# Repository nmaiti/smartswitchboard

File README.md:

# smartswitchboard

This repo contains all capsense design files

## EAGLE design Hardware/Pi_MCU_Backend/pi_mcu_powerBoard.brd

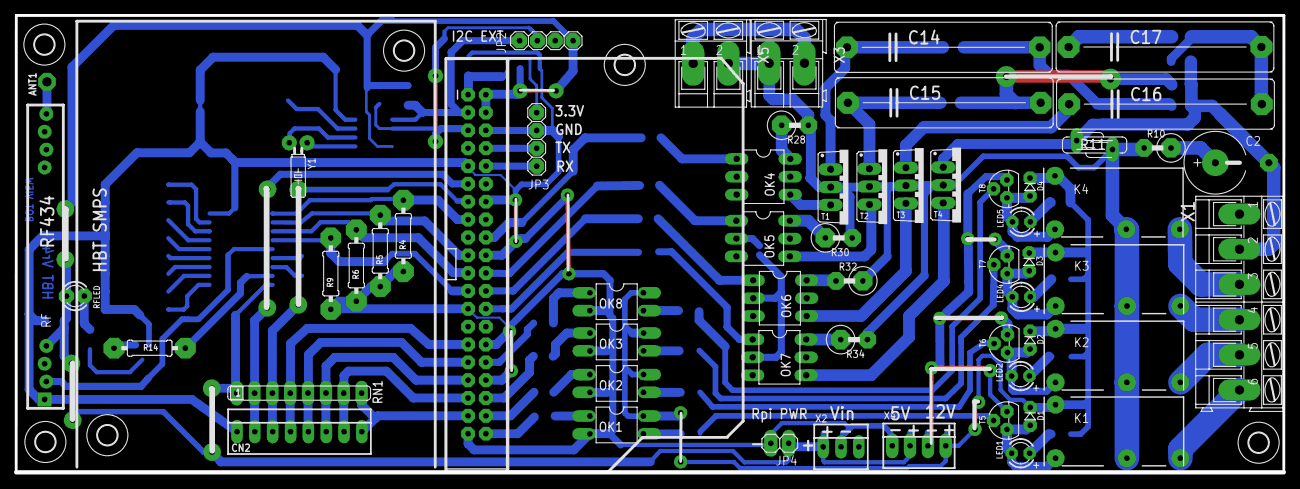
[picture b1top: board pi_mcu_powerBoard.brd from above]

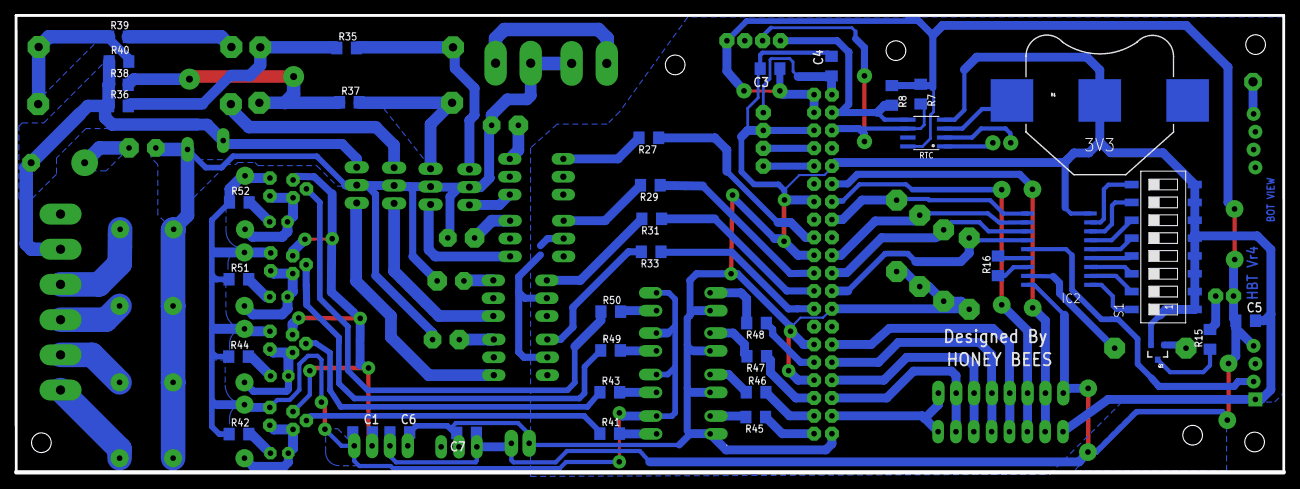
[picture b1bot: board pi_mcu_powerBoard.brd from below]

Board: 2 copper layers, 180.5 x 64.9 mm, 102 parts (37 on the bottom side), 93 nets.

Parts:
ANT1: PAD-01
B1: BATTCON_20MM
C1, C3, C4, C5, C6, C7: C1206
C2: E5R
C14, C16: 2.2uF/250VAC; C27.5B9
C15, C17: 3.3uF/250VAC; C27.5B9
CN2: Capsense I/P; 22-23-2081
D1, D2, D3, D4: D-2.5
IC2: HT680D; SOP18
JP1: RASPBERRYPI-B+-GPIO; 2X20-SHROUDED
JP2, JP3: 1X04
JP4: 1X02
K1, K2, K3, K4: RE030012; RE-SCHRACK
LED1, LED2, LED4, LED5: LED3MM
OK1, OK2, OK3, OK8: PC817; DIL04
OK4, OK5, OK6, OK7: MOC3041M; DIL06
Q2: MMBT2222A; SOT23-3
R4, R5, R6, R9: 0207/10
R7, R8: 4k7; 1206
R10: 0411V
R11: S07K11
R14: 10K; 0207/10
R15, R27, R29, R31, R33: 560R; 1206
R16: 33k; 1206
R28, R30, R32, R34: 470R/0.5W; 0411V
R35, R37, R39: 220K; 1206
R36, R38, R40: 2E2; 1206
R41, R42, R43, R44, R45, R46, R47, R48, R49, R50, R51, R52: 1k; 1206
RF: RF-LINK_RX
RFLED: LED3MM
RN1: SIL8
RTC: DS1307SO8; SO08
S1: SWS008; SMS-008
T1, T2, T3, T4: BTB16-V; TO220BV
T5, T6, T7, T8: BC547; TO92
U$3, U$4, U$5, U$6, U$7, U$8: 2,8
X1: AK300/6
X2: 22-23-2031
X3, X5: AK300/2
X4: 22-23-2041
Y1: 32.768KHz; TC26H

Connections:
(DIN)TE: IC2.14, RF.DATA@1
(VT)ADOUT: IC2.17, R14.2
+3V3: C4.1, JP1.1, JP1.17, JP3.1
+5V: C3.1, C5.1, C6.1, C7.1, IC2.18, JP1.2, JP1.4, JP2.1, JP4.1, R7.1, R8.1, RF.+5V@1, RFLED.A, RN1.1, RTC.8, X2.1, X4.2
+12V: C1.1, D1.C, D2.C, D3.C, D4.C, K1.A2, K2.A2, K3.A2, K4.A2, OK1.4, OK2.4, OK3.4, OK8.4, R42.1, R44.1, R51.1, R52.1, X4.4
-12V: C1.2, T5.1, T6.1, T7.1, T8.1, X4.3
A0: IC2.1, S1.16
A1: IC2.2, S1.15
A2: IC2.3, S1.14
A3: IC2.4, S1.13
A4: IC2.5, S1.12
A5: IC2.6, S1.11
A6: IC2.7, S1.10
A7: IC2.8, S1.9
DOWN: CN2.7, JP1.35, RN1.7
FAN_ON/OFF: CN2.8, JP1.37, RN1.8
FAN_REG: C2.-, R11.1, R36.1, R38.1, R40.1, T4.T1, X1.2
GND: B1.2, C3.2, C4.2, C5.2, C6.2, C7.2, CN2.1, IC2.9, JP1.6, JP1.9, JP1.14, JP1.20, JP1.25, JP1.30, JP1.34, JP1.39, JP2.2, JP3.2, JP4.2, OK1.2, OK2.2, OK3.2, OK4.2, OK5.2, OK6.2, OK7.2, OK8.2, Q2.2, R4.1, R5.1, R6.1, R9.1, RF.GND@1, RTC.4, S1.1, S1.2, S1.3, S1.4, S1.5, S1.6, S1.7, S1.8, X2.2, X4.1
L1: JP1.40, R45.1
L2: JP1.38, R46.2
L3: JP1.36, R47.1
L4: JP1.32, R48.1
LEVEL1: JP1.18, R27.1
LEVEL2: JP1.22, R29.1
LEVEL3: JP1.24, R31.1
LEVEL4: JP1.26, R33.1
LINE: K1.14, K2.14, K3.14, K4.14, R10.2, R11.2, R28.2, R30.2, R32.1, R34.2, T1.T2, T2.T2, T3.T2, T4.T2, X3.1, X5.2
unnamed: OK6.1, R31.2
unnamed: OK4.1, R27.2
unnamed: OK5.1, R29.2
unnamed: OK4.6, R28.1
unnamed: OK7.1, R33.2
unnamed: OK1.3, R41.2
unnamed: R41.1, T5.2
unnamed: D1.A, K1.A1, LED1.K, T5.3
unnamed: LED1.A, R42.2
unnamed: OK1.1, R45.2
unnamed: RTC.2, Y1.2
unnamed: OK2.1, R46.1
unnamed: OK2.3, R43.2
unnamed: R43.1, T6.2
unnamed: C2.+, R10.1
unnamed: D2.A, K2.A1, LED2.K, T6.3
unnamed: Q2.1, R14.1
unnamed: RTC.1, Y1.1
unnamed: K3.11, X1.4
unnamed: B1.1, RTC.3
unnamed: Q2.3, R15.1
unnamed: LED2.A, R44.2
unnamed: K1.11, X1.6
unnamed: R15.2, RFLED.K
unnamed: K2.11, X1.5
unnamed: OK5.6, R30.1
unnamed: OK6.6, R32.2
unnamed: ANT1.1, RF.ANT
unnamed: OK3.1, R47.2
unnamed: OK8.3, R50.2
unnamed: OK7.6, R34.1
unnamed: OK3.3, R49.2
unnamed: R49.1, T7.2
unnamed: R50.1, T8.2
unnamed: D3.A, K3.A1, LED4.K, T7.3
unnamed: K4.11, X1.3
unnamed: LED4.A, R51.2
unnamed: D4.A, K4.A1, LED5.K, T8.3
unnamed: LED5.A, R52.2
unnamed: OK8.1, R48.2
unnamed: OK4.4, T1.G
unnamed: C14.1, R35.2, T1.T1
unnamed: C14.2, R35.1, R36.2
unnamed: OK5.4, T2.G
unnamed: C15.1, R37.2, T2.T1
unnamed: C15.2, R37.1, R38.2
unnamed: OK6.4, T3.G
unnamed: C16.1, C17.1, R39.2, T3.T1
unnamed: C16.2, C17.2, R39.1, R40.2
unnamed: OK7.4, T4.G
NEUTRAL: X1.1, X3.2, X5.1
OSC1: IC2.16, R16.1
OSC2: IC2.15, R16.2
RFD0: IC2.10, JP1.15, R4.2
RFD1: IC2.11, JP1.19, R5.2
RFD2: IC2.12, JP1.21, R6.2
RFD3: IC2.13, JP1.23, R9.2
RX: JP1.10, JP3.4
SCL: JP1.5, JP2.3, R7.2, RTC.6
SDA: JP1.3, JP2.4, R8.2, RTC.5
SW-1: CN2.2, JP1.11, RN1.2
SW-2: CN2.3, JP1.13, RN1.3
SW-3: CN2.4, JP1.29, RN1.4
SW-4: CN2.5, JP1.31, RN1.5
TX: JP1.8, JP3.3
UP: CN2.6, JP1.33, RN1.6

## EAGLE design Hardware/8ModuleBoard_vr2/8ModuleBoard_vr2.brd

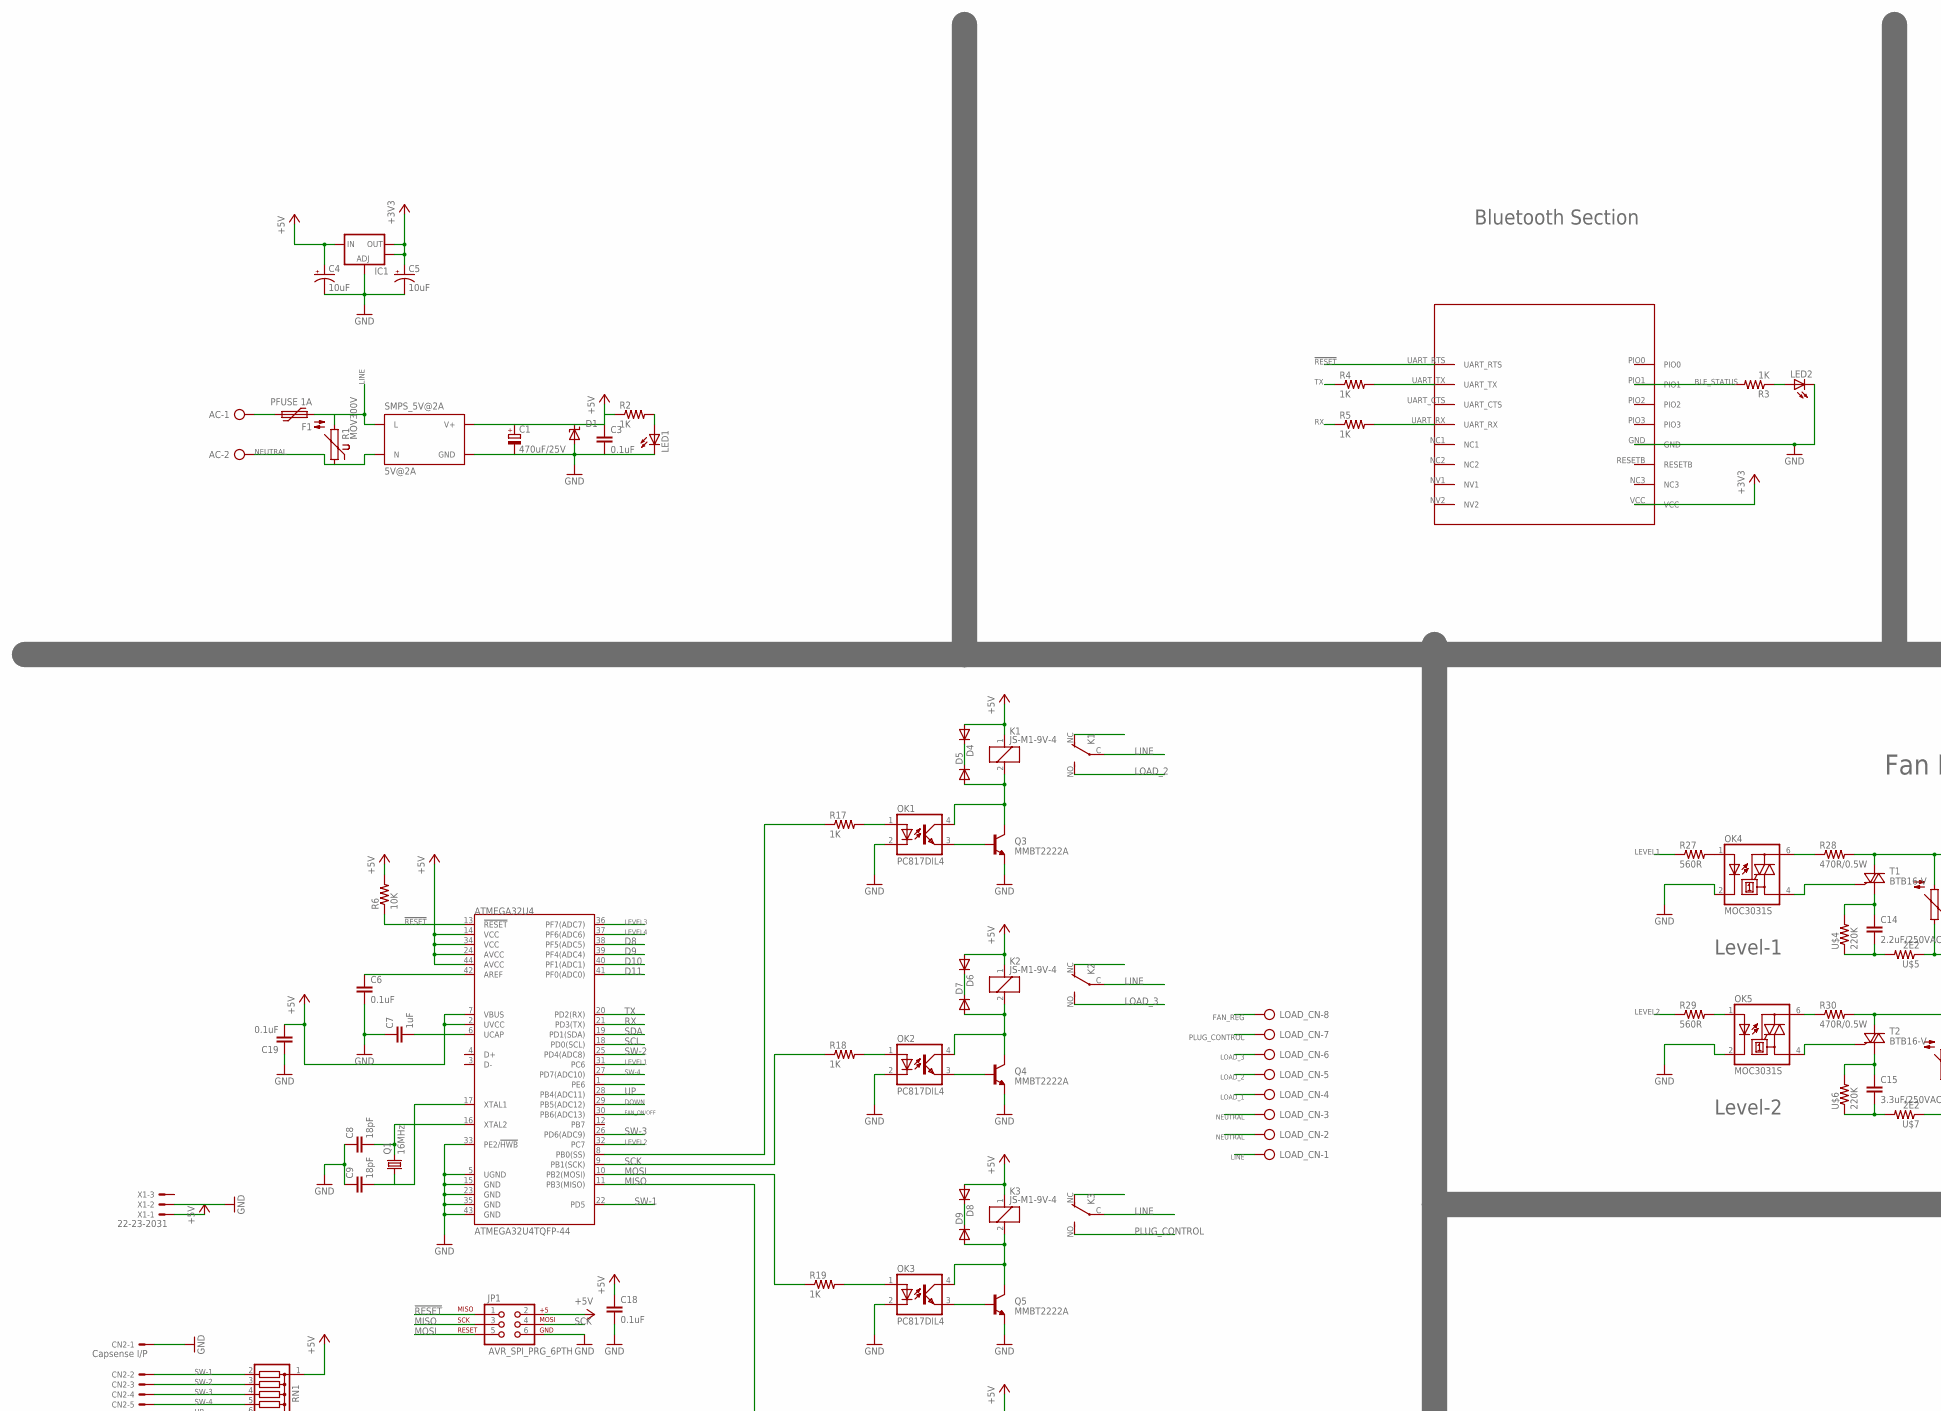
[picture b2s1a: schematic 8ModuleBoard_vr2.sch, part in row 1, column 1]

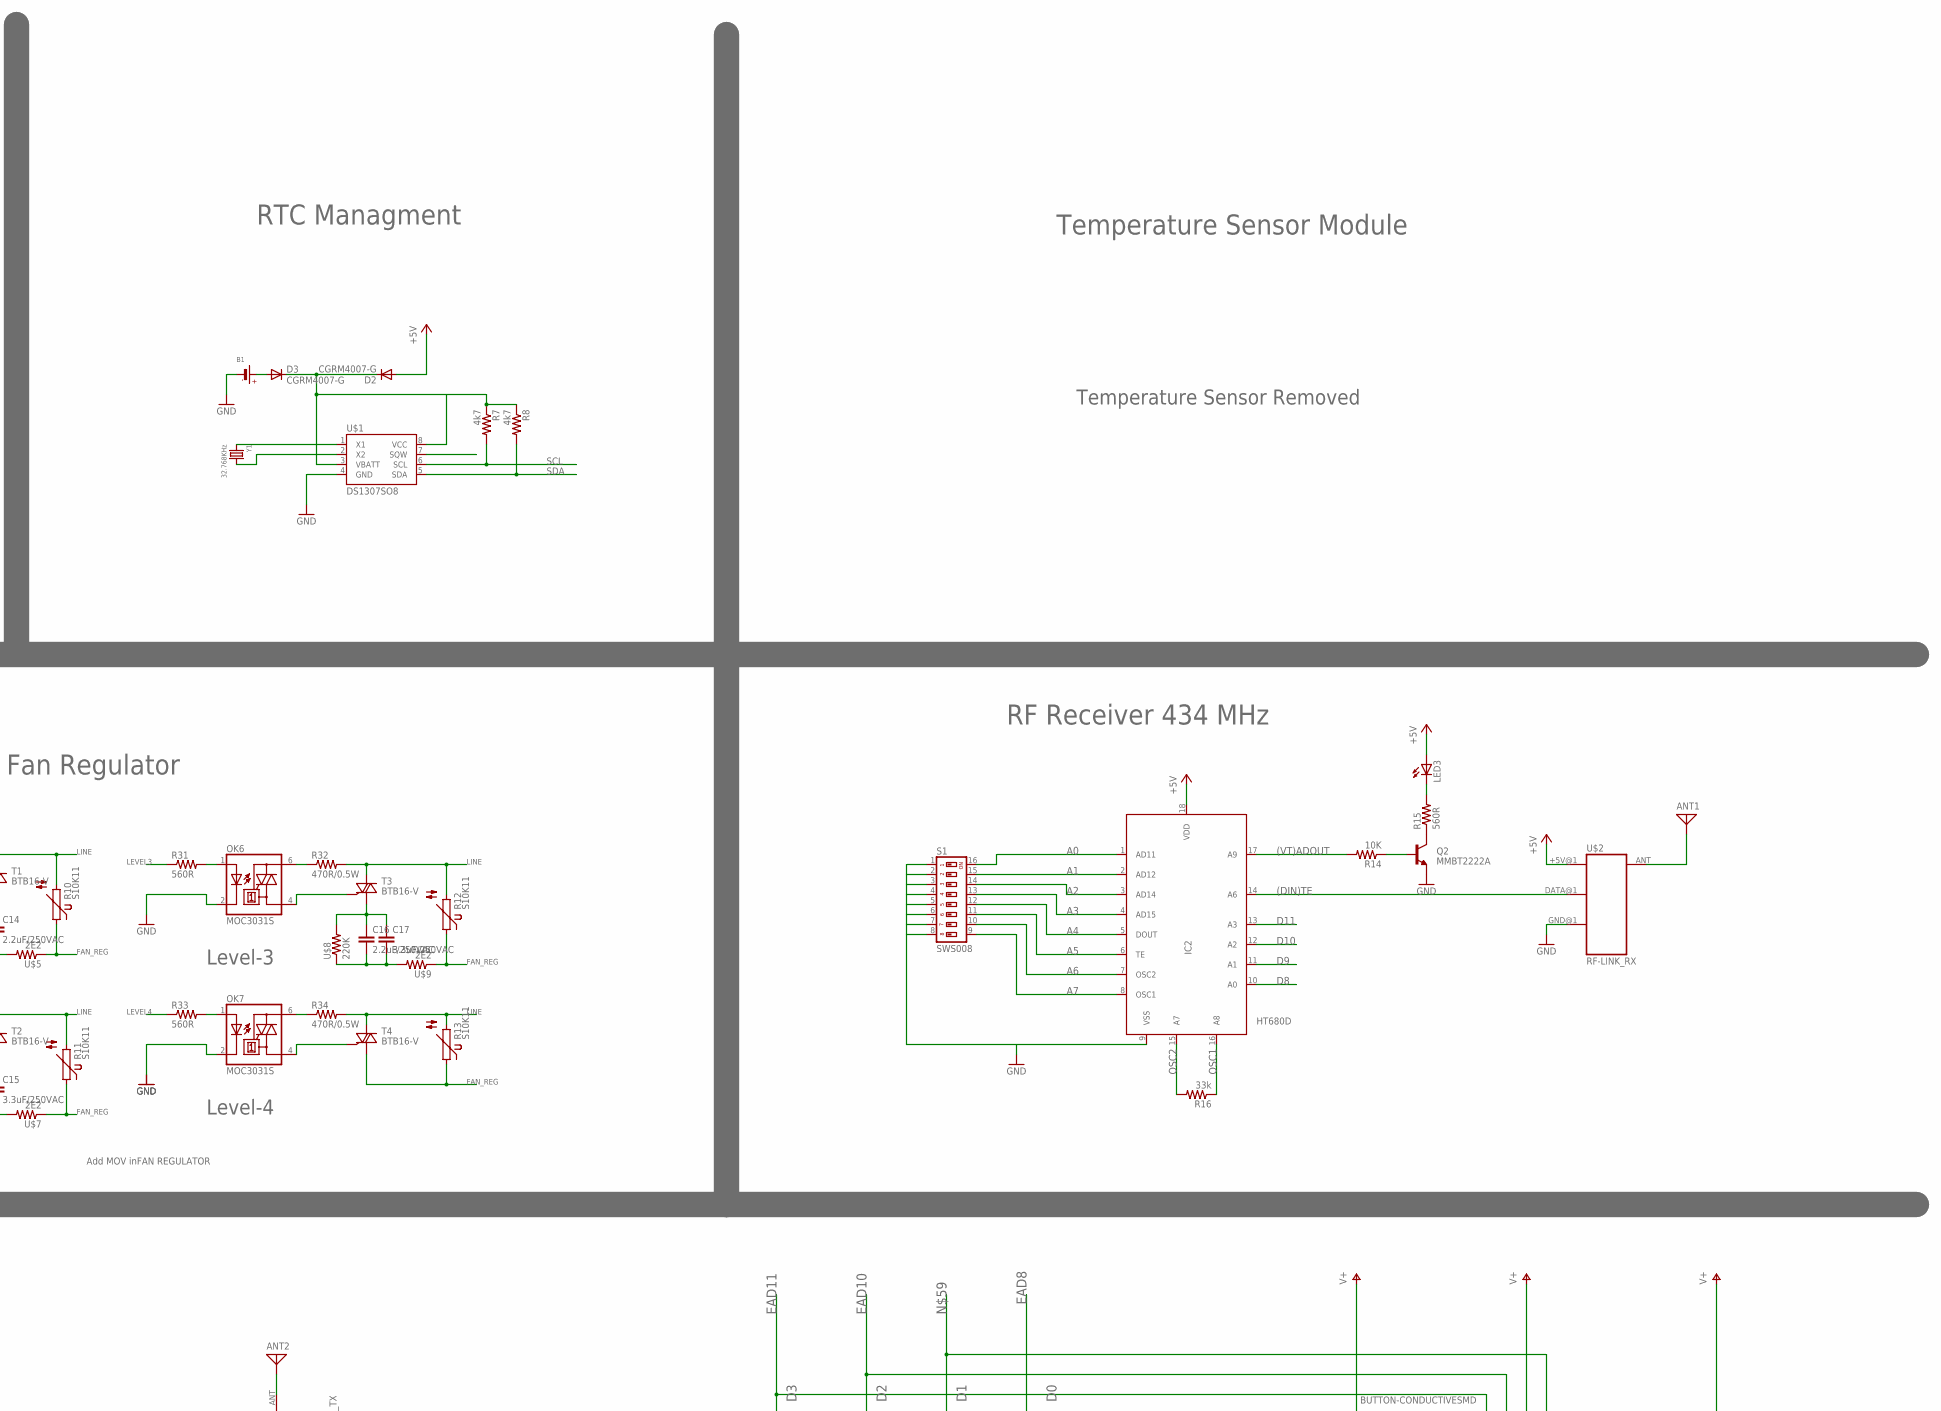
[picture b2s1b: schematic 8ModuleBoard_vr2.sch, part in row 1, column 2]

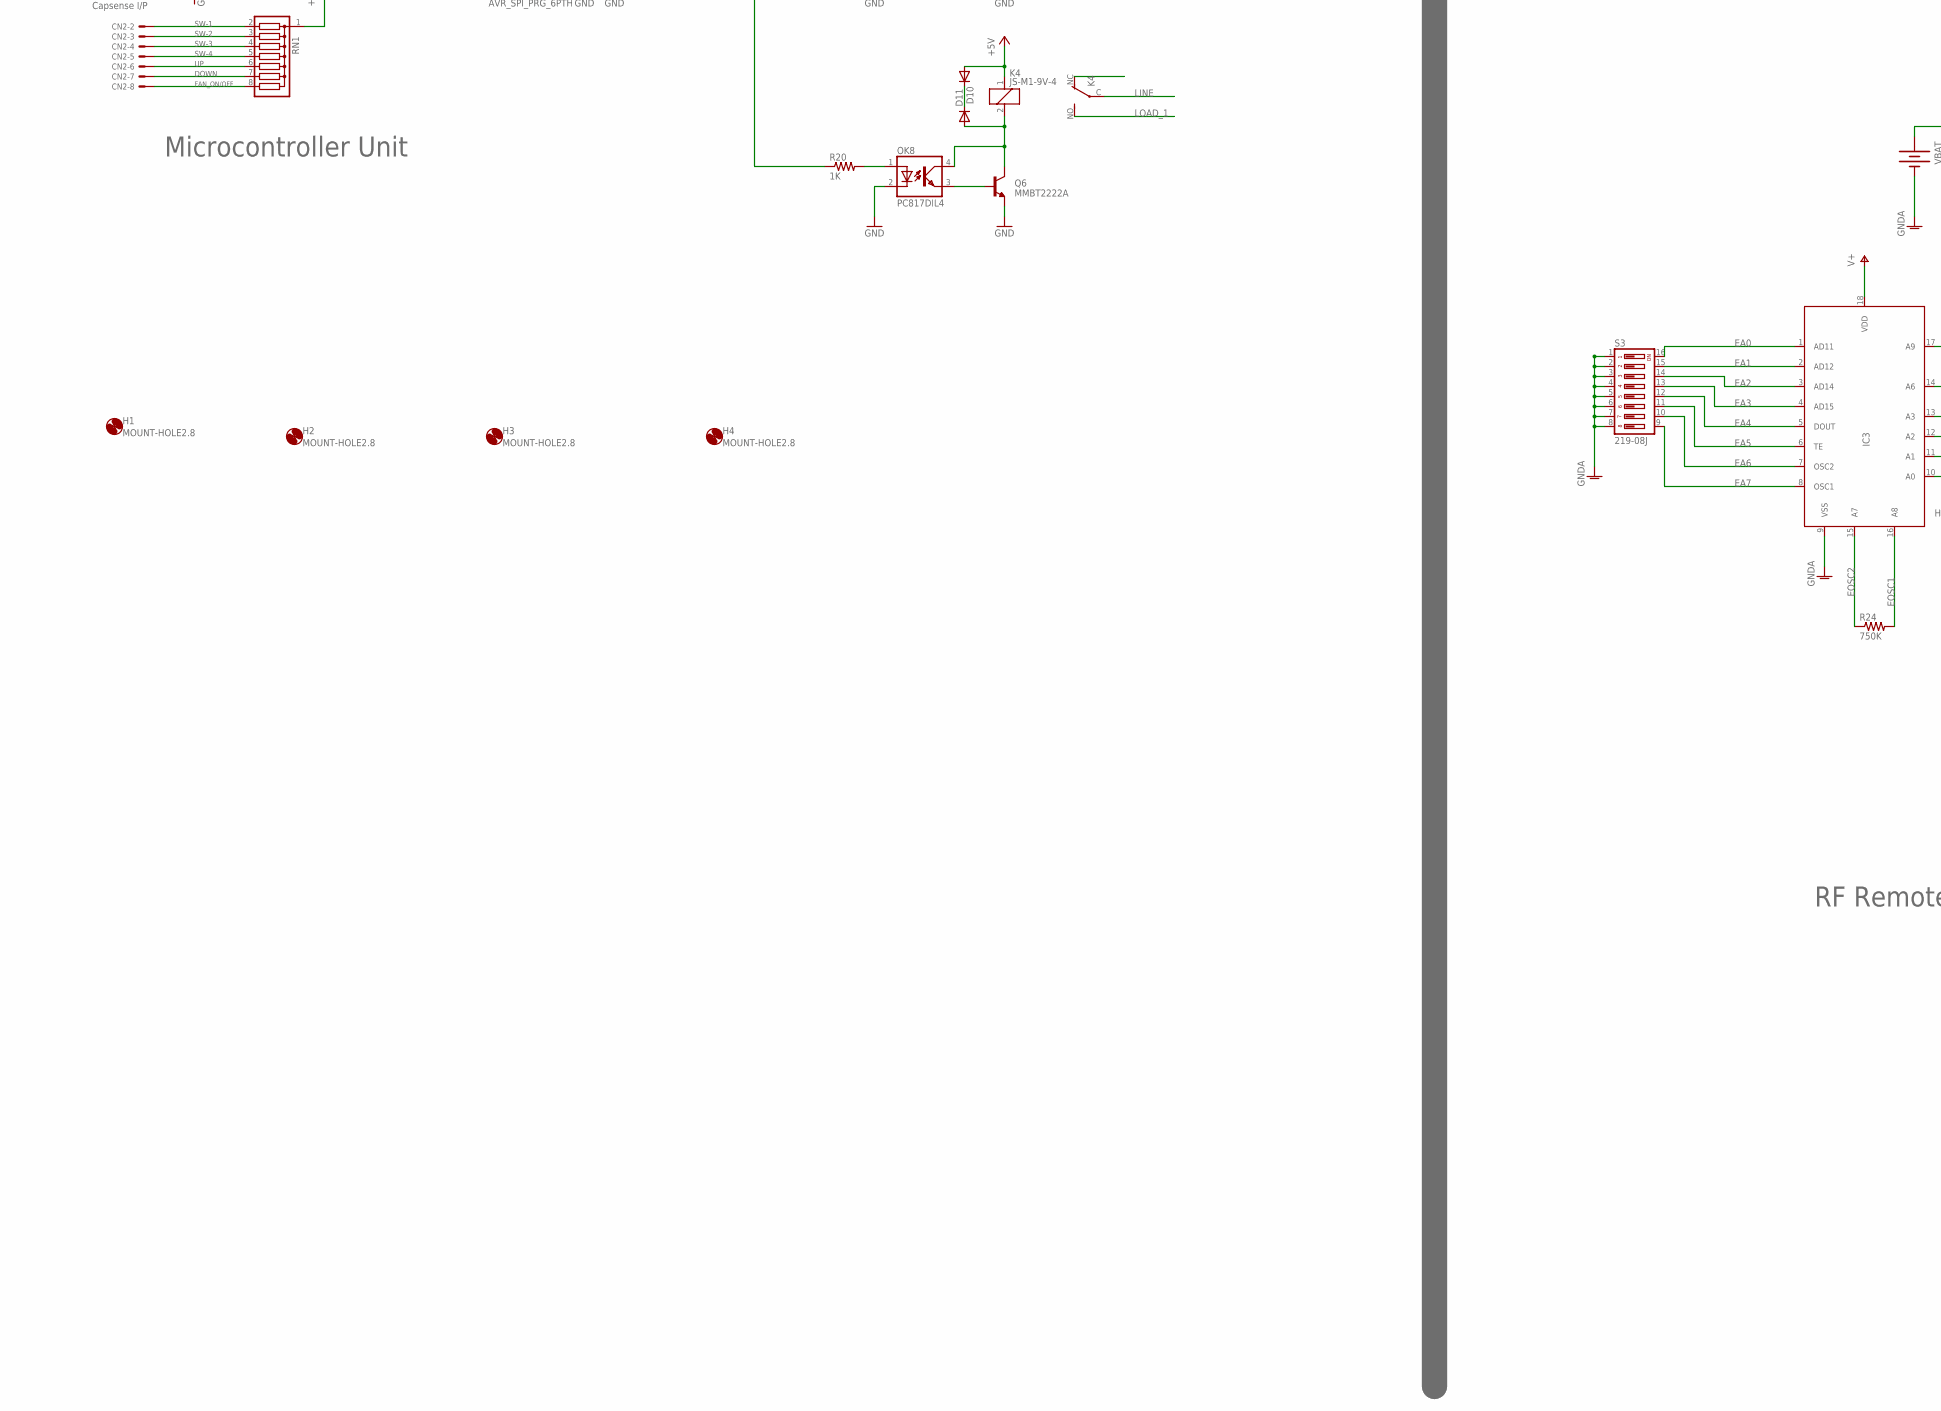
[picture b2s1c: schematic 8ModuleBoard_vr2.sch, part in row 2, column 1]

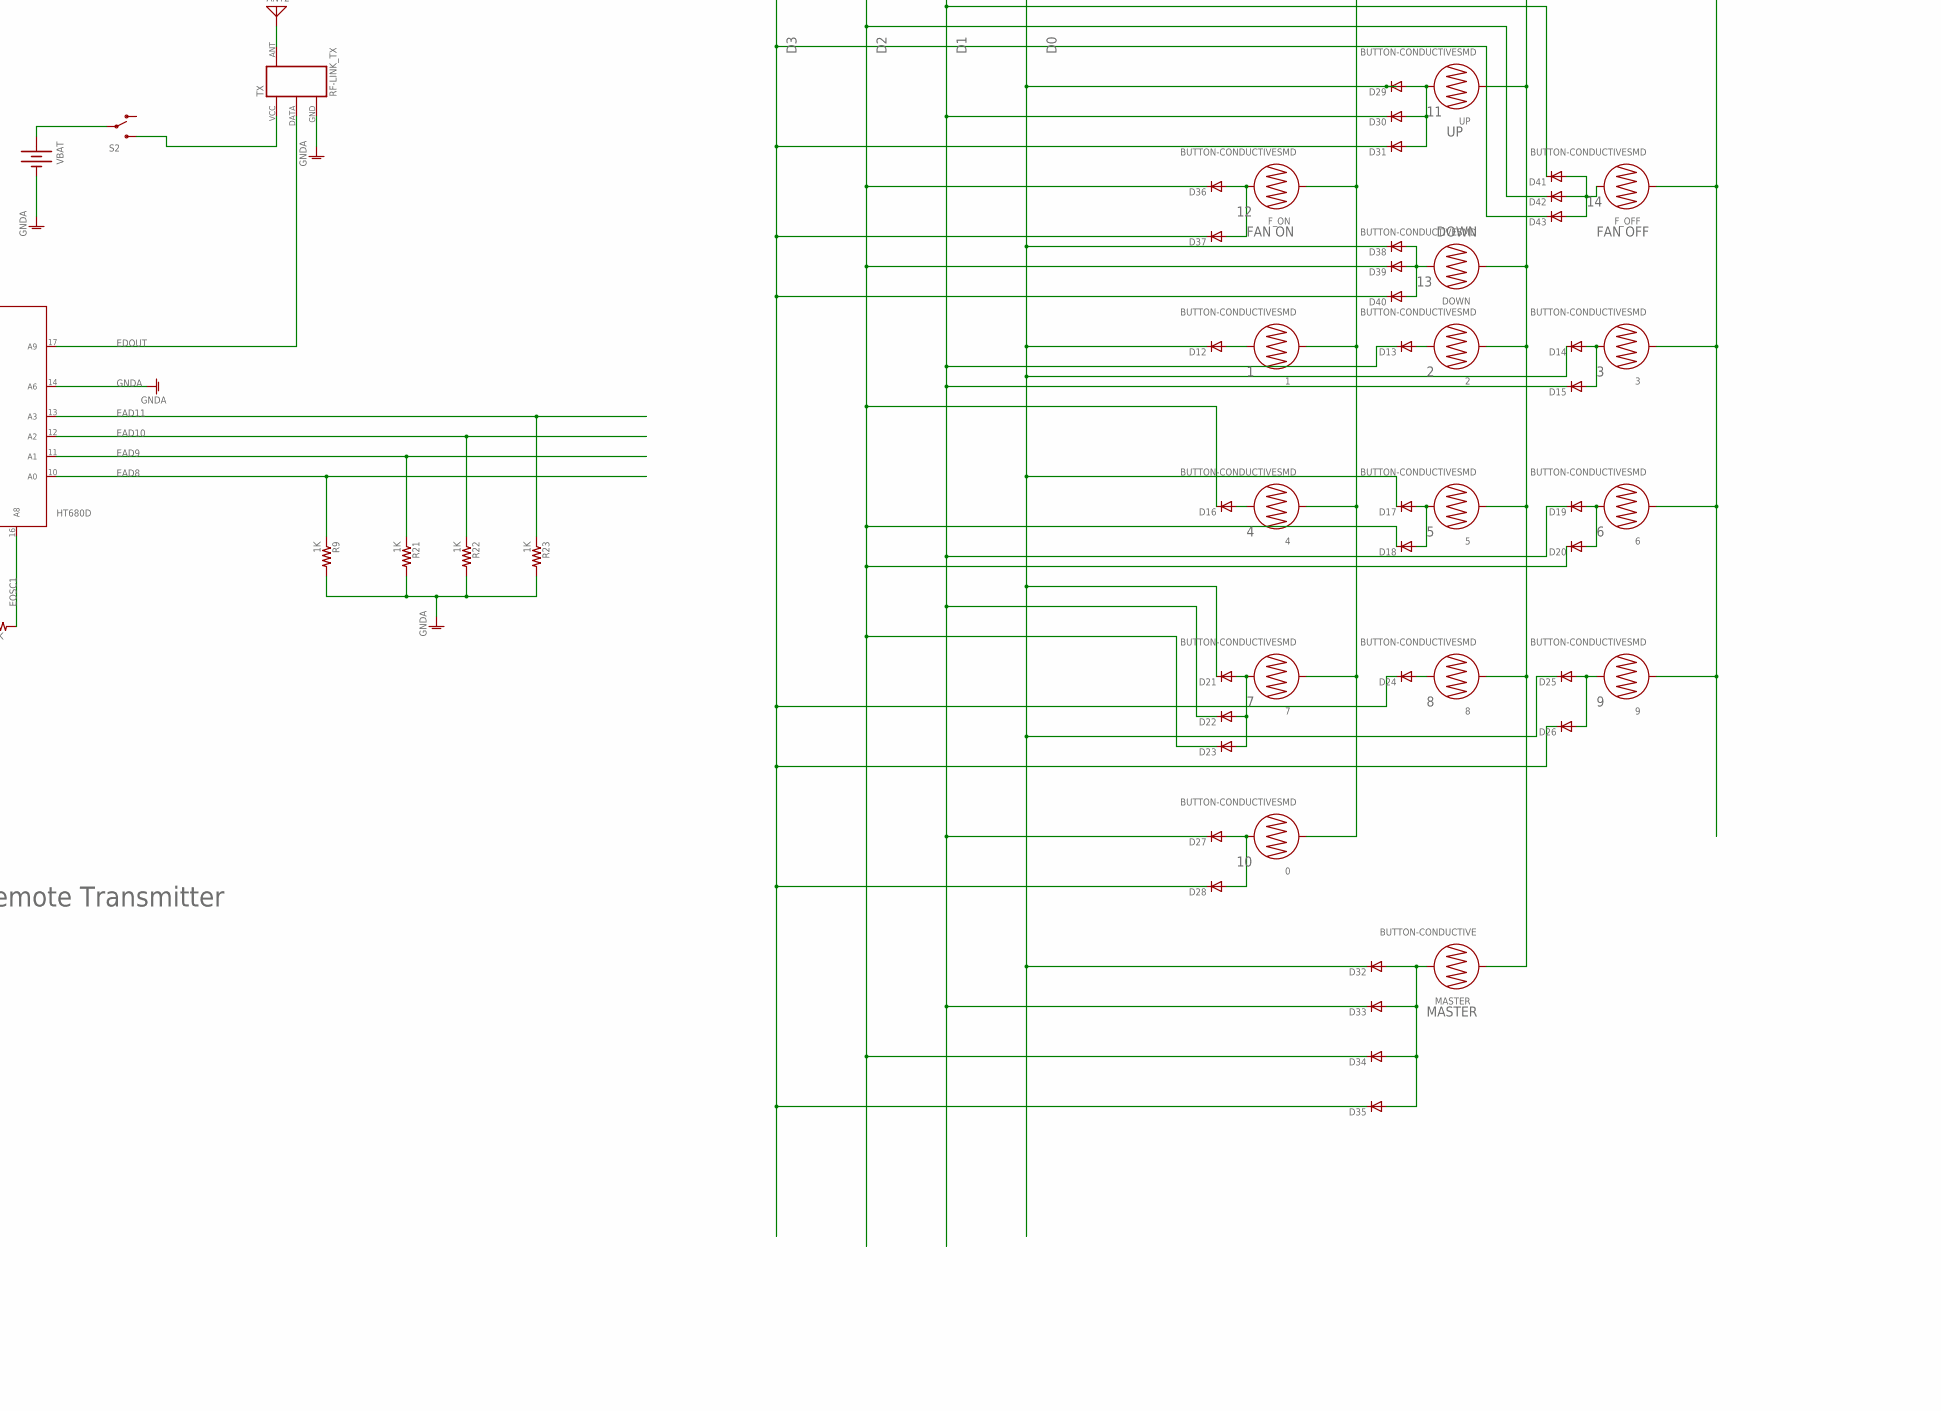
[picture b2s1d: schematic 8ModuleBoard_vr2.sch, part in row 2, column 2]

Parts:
0, 1, 2, 3, 4, 5, 6, 7, 8, 9: BUTTON-CONDUCTIVESMD; BUTTON-CONDUCTIVE
AC: AK300/2
ANT1, ANT2: ANTENNA; PAD-01
ATMEGA32U4: ATMEGA32U4TQFP-44; TQFP44
B1: BATTERYCR2032; CR2032
C1: 470uF/25V; E5-8,5
C3, C6, C18, C19: 0.1uF; 1206
C4, C5: 10uF; EIA3216
C7: 1uF; 1206
C8, C9: 18pF; 1206
C14, C16: 2.2uF/250VAC; C27.5B9
C15, C17: 3.3uF/250VAC; C27.5B9
CN2: Capsense I/P; 22-23-2081
D1: SUPPRESSOR-SMBJ; SMBJ
D2, D3: CGRM4007-G; SOD-123_MINI-SMA
D4, D5, D6, D7, D8, D9, D10, D11, D12, D13, D14, D15, D16, D17, D18, D19, D20, D21, D22, D23, D24, D25, D26, D27, D28, D29, D30, D31, D32, D33, D34, D35, D36, D37, D38, D39, D40, D41, D42, D43: DIODE-SOD123; SOD123
DOWN: BUTTON-CONDUCTIVESMD; BUTTON-CONDUCTIVE
F1: PFUSE 1A; MF-5,1B
F_OFF: BUTTON-CONDUCTIVESMD; BUTTON-CONDUCTIVE
F_ON: BUTTON-CONDUCTIVESMD; BUTTON-CONDUCTIVE
H1, H2, H3, H4: MOUNT-HOLE2.8; 2,8
IC1: V_REG_LM1117SOT223; SOT223
IC2, IC3: HT680D; SOP18
JP1: AVR_SPI_PRG_6PTH; 2X3
K1, K2, K3, K4: JS-M1-9V-4; JS-M
LED1, LED2, LED3: LEDSML1206; SML1206
LOAD_CN: AK300/8
MASTER: BUTTON-CONDUCTIVE; BUTTON-CONDUCTIVE-MINI
OK1, OK2, OK3, OK8: PC817DIL4; DIL4-SMD
OK4: MOC3031S; DIL6-SMD
OK5, OK6, OK7: MOC3031S; DIL6-SMD; MPN MOC3031SM
Q1: 16MHz; HC49UP
Q2, Q3, Q4, Q5, Q6: MMBT2222A; SOT23-3
R1: MOV300V; S10K11
R2, R3, R4, R5, R9, R17, R18, R19, R20, R21, R22, R23: 1K; 1206
R6, R14: 10K; 1206
R7, R8: 4k7; 1206
R10, R11, R12, R13: S10K11
R15, R27, R29, R31, R33: 560R; 1206
R16: 33k; 1206
R24: 750K; 1206
R28, R30, R32, R34: 470R/0.5W; 0411V
RN1: G07R; SIL8
S1: SWS008; SMS-008
S2: SWITCH-SPDT-SMD-A; SWITCH-SPST-SMD-A
S3: 219-08J; CTS-219-08J
SMPS_5V@2A: 5V@2A; MKS1854-6-0-404
T1, T2, T3, T4: BTB16-V; TO220BV
TX: RF-LINK_TX
U$1: DS1307SO8; SO08
U$2: RF-LINK_RX
U$3: HM-11
U$4, U$6, U$8: 220K; 1206
U$5, U$7, U$9: 2E2; 1206
UP: BUTTON-CONDUCTIVESMD; BUTTON-CONDUCTIVE
VBAT: BATTERY20SMD; BATTCON_20MM
X1: 22-23-2031
Y1: 32.768KHz; CRYSTAL_CYL_2X6MM_SMT

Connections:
!RESET: ATMEGA32U4.13 (!RESET), JP1.1, R6.1, U$3.UART_RTS
(DIN)TE: IC2.14 (A6), U$2.DATA@1 (DATA)
(VT)ADOUT: IC2.17 (A9), R14.2
+3V3: C5.A (+), IC1.2 (OUT), IC1.4 (OUT), U$3.VCC
+5V: ATMEGA32U4.2 (UVCC), ATMEGA32U4.7 (VBUS), ATMEGA32U4.14 (VCC), ATMEGA32U4.24 (AVCC), ATMEGA32U4.34 (VCC), ATMEGA32U4.44 (AVCC), C1.+, C3.1, C4.A (+), C18.1, C19.2, D1.C, D2.A, D4.A, D6.A, D8.A, D10.A, IC1.3 (IN), IC2.18 (VDD), JP1.2, K1.1, K2.1, K3.1, K4.1, LED3.A, R2.1, R6.2, RN1.1, SMPS_5V@2A.3 (V+), U$2.+5V@1 (+5V), X1.1
A0: IC2.1 (AD11), S1.16
A1: IC2.2 (AD12), S1.15
A2: IC2.3 (AD14), S1.14
A3: IC2.4 (AD15), S1.13
A4: IC2.5 (DOUT), S1.12
A5: IC2.6 (TE), S1.11
A6: IC2.7 (OSC2), S1.10
A7: IC2.8 (OSC1), S1.9
BLE_STATUS: R3.2, U$3.PIO1
D8: ATMEGA32U4.38 (PF5(ADC5)), IC2.10 (A0)
D9: ATMEGA32U4.39 (PF4(ADC4)), IC2.11 (A1)
D10: ATMEGA32U4.40 (PF1(ADC1)), IC2.12 (A2)
D11: ATMEGA32U4.41 (PF0(ADC0)), IC2.13 (A3)
DOWN: ATMEGA32U4.29 (PB5(ADC12)), CN2.7, RN1.7
EA0: IC3.1 (AD11), S3.16
EA1: IC3.2 (AD12), S3.15
EA2: IC3.3 (AD14), S3.14
EA3: IC3.4 (AD15), S3.13
EA4: IC3.5 (DOUT), S3.12
EA5: IC3.6 (TE), S3.11
EA6: IC3.7 (OSC2), S3.10
EA7: IC3.8 (OSC1), S3.9
EAD8: D12.C, D14.C, D17.C, D21.C, D25.C, D29.C, D32.C, D38.C, IC3.10 (A0), R9.1
EAD9: IC3.11 (A1), R21.1
EAD10: D16.C, D18.C, D20.C, D23.C, D34.C, D36.C, D39.C, D42.C, IC3.12 (A2), R22.1
EAD11: D24.C, D26.C, D28.C, D31.C, D35.C, D37.C, D40.C, D43.C, IC3.13 (A3), R23.1
EDOUT: IC3.17 (A9), TX.DATA
EOSC1: IC3.16 (A8), R24.2
EOSC2: IC3.15 (A7), R24.1
FAN_ON/OFF: ATMEGA32U4.30 (PB6(ADC13)), CN2.8, RN1.8
FAN_REG: LOAD_CN.8, R10.1, R11.1, R12.1, R13.1, T4.T1 (A1), U$5.1, U$7.1, U$9.1
GND: ATMEGA32U4.5 (UGND), ATMEGA32U4.15 (GND), ATMEGA32U4.23 (GND), ATMEGA32U4.33 (PE2/!HWB), ATMEGA32U4.35 (GND), ATMEGA32U4.43 (GND), B1.-, C1.-, C3.2, C4.C (-), C5.C (-), C6.2, C7.1, C8.1, C9.1, C18.2, C19.1, CN2.1, D1.A, IC1.1 (ADJ), IC2.9 (VSS), JP1.6, LED1.C, LED2.C, OK1.2 (C), OK2.2 (C), OK3.2 (C), OK4.2 (C), OK5.2 (C), OK6.2 (C), OK7.2 (C), OK8.2 (C), Q2.2 (E), Q3.2 (E), Q4.2 (E), Q5.2 (E), Q6.2 (E), S1.1, S1.2, S1.3, S1.4, S1.5, S1.6, S1.7, S1.8, SMPS_5V@2A.4 (GND), U$1.4 (GND), U$2.GND@1 (GND), U$3.GND, X1.2
GNDA: IC3.9 (VSS), IC3.14 (A6), R9.2, R21.2, R22.2, R23.2, S3.1, S3.2, S3.3, S3.4, S3.5, S3.6, S3.7, S3.8, TX.GND, VBAT.2 (-)
LEVEL1: ATMEGA32U4.31 (PC6), R27.1
LEVEL2: ATMEGA32U4.32 (PC7), R29.1
LEVEL3: ATMEGA32U4.36 (PF7(ADC7)), R31.1
LEVEL4: ATMEGA32U4.37 (PF6(ADC6)), R33.1
LINE: F1.1, K1.C, K2.C, K3.C, K4.C, LOAD_CN.1, R1.2, R10.2, R11.2, R12.2, R13.2, R28.2, R30.2, R32.2, R34.2, SMPS_5V@2A.1 (L), T1.T2 (A2), T2.T2 (A2), T3.T2 (A2), T4.T2 (A2)
LOAD_1: K4.NO (S), LOAD_CN.4
LOAD_2: K1.NO (S), LOAD_CN.5
LOAD_3: K2.NO (S), LOAD_CN.6
MISO: ATMEGA32U4.11 (PB3(MISO)), JP1.3, R20.1
MOSI: ATMEGA32U4.10 (PB2(MOSI)), JP1.5, R19.1
unnamed: OK6.1 (A), R31.2
unnamed: OK4.1 (A), R27.2
unnamed: OK5.1 (A), R29.2
unnamed: OK4.6 (A2), R28.1
unnamed: OK7.1 (A), R33.2
unnamed: R4.2, U$3.UART_TX
unnamed: ATMEGA32U4.6 (UCAP), C7.2
unnamed: Q2.1 (B), R14.1
unnamed: LED2.A, R3.1
unnamed: ATMEGA32U4.42 (AREF), C6.1
unnamed: R5.2, U$3.UART_RX
unnamed: U$1.1 (X1), Y1.1
unnamed: U$1.2 (X2), Y1.2
unnamed: D2.C, D3.C, R7.1, R8.1, U$1.3 (VBATT), U$1.8 (VCC)
unnamed: LED1.A, R2.2
unnamed: B1.+, D3.A
unnamed: 1.2, D12.A
unnamed: 2.2, D13.A
unnamed: ATMEGA32U4.16 (XTAL2), C8.2, Q1.2
unnamed: ATMEGA32U4.17 (XTAL1), C9.2, Q1.1
unnamed: Q2.3 (C), R15.1
unnamed: S2.2, VBAT.1 (+)
unnamed: LED3.C, R15.2
unnamed: S2.3 (S), TX.VCC (+5V)
unnamed: OK5.6 (A2), R30.1
unnamed: OK6.6 (A2), R32.1
unnamed: ANT1.1, U$2.ANT
unnamed: OK1.3 (EMIT), Q3.1 (B)
unnamed: D5.A, K1.2, OK1.4 (COL), Q3.3 (C)
unnamed: OK7.6 (A2), R34.1
unnamed: 3.2, D14.A, D15.A
unnamed: AC.1, F1.2
unnamed: D4.C, D5.C
unnamed: ANT2.1, TX.ANT
unnamed: OK1.1 (A), R17.2
unnamed: 4.2, D16.A
unnamed: OK2.3 (EMIT), Q4.1 (B)
unnamed: 5.2, D17.A, D18.A
unnamed: D7.A, K2.2, OK2.4 (COL), Q4.3 (C)
unnamed: D6.C, D7.C
unnamed: 6.2, D19.A, D20.A
unnamed: 7.2, D21.A, D22.A, D23.A
unnamed: OK2.1 (A), R18.2
unnamed: OK3.3 (EMIT), Q5.1 (B)
unnamed: 0.2, D27.A, D28.A
unnamed: D9.A, K3.2, OK3.4 (COL), Q5.3 (C)
unnamed: OK4.4 (A1), T1.G
unnamed: C14.1, T1.T1 (A1), U$4.2
unnamed: C14.2, U$4.1, U$5.2
unnamed: D8.C, D9.C
unnamed: D13.C, D15.C, D19.C, D22.C, D27.C, D30.C, D33.C, D41.C
unnamed: D29.A, D30.A, D31.A, UP.2
unnamed: 8.2, D24.A
unnamed: OK5.4 (A1), T2.G
unnamed: C15.1, T2.T1 (A1), U$6.2
unnamed: C15.2, U$6.1, U$7.2
unnamed: OK3.1 (A), R19.2
unnamed: OK8.3 (EMIT), Q6.1 (B)
unnamed: D11.A, K4.2, OK8.4 (COL), Q6.3 (C)
unnamed: D36.A, D37.A, F_ON.2
unnamed: D10.C, D11.C
unnamed: OK6.4 (A1), T3.G
unnamed: C16.1, C17.1, T3.T1 (A1), U$8.2
unnamed: C16.2, C17.2, U$8.1, U$9.2
unnamed: 9.2, D25.A, D26.A
unnamed: D38.A, D39.A, D40.A, DOWN.2
unnamed: D32.A, D33.A, D34.A, D35.A, MASTER.2
unnamed: OK8.1 (A), R20.2
unnamed: OK7.4 (A1), T4.G
unnamed: D41.A, D42.A, D43.A, F_OFF.2
unnamed: ATMEGA32U4.8 (PB0(SS)), R17.1
NEUTRAL: AC.2, LOAD_CN.2, LOAD_CN.3, R1.1, SMPS_5V@2A.2 (N)
OSC1: IC2.16 (A8), R16.1
OSC2: IC2.15 (A7), R16.2
PLUG_CONTROL: K3.NO (S), LOAD_CN.7
RX: ATMEGA32U4.21 (PD3(TX)), R5.1
SCK: ATMEGA32U4.9 (PB1(SCK)), JP1.4, R18.1
SCL: ATMEGA32U4.18 (PD0(SCL)), R7.2, U$1.6 (SCL)
SDA: ATMEGA32U4.19 (PD1(SDA)), R8.2, U$1.5 (SDA)
SW-1: ATMEGA32U4.22 (PD5), CN2.2, RN1.2
SW-2: ATMEGA32U4.25 (PD4(ADC8)), CN2.3, RN1.3
SW-3: ATMEGA32U4.26 (PD6(ADC9)), CN2.4, RN1.4
SW-4: ATMEGA32U4.27 (PD7(ADC10)), CN2.5, RN1.5
TX: ATMEGA32U4.20 (PD2(RX)), R4.1
UP: ATMEGA32U4.28 (PB4(ADC11)), CN2.6, RN1.6
V+: 0.1, 1.1, 2.1, 3.1, 4.1, 5.1, 6.1, 7.1, 8.1, 9.1, DOWN.1, F_OFF.1, F_ON.1, IC3.18 (VDD), MASTER.1, UP.1

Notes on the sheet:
Microcontroller Unit
Level-1
Level-2
Level-3
Level-4
Fan Regulator
Bluetooth Section
Add MOV inFAN REGULATOR
RTC Managment
Temperature Sensor Module
RF Receiver 434 MHz
Temperature Sensor Removed
MASTER
FAN ON
FAN OFF
DOWN
RF Remote Transmitter

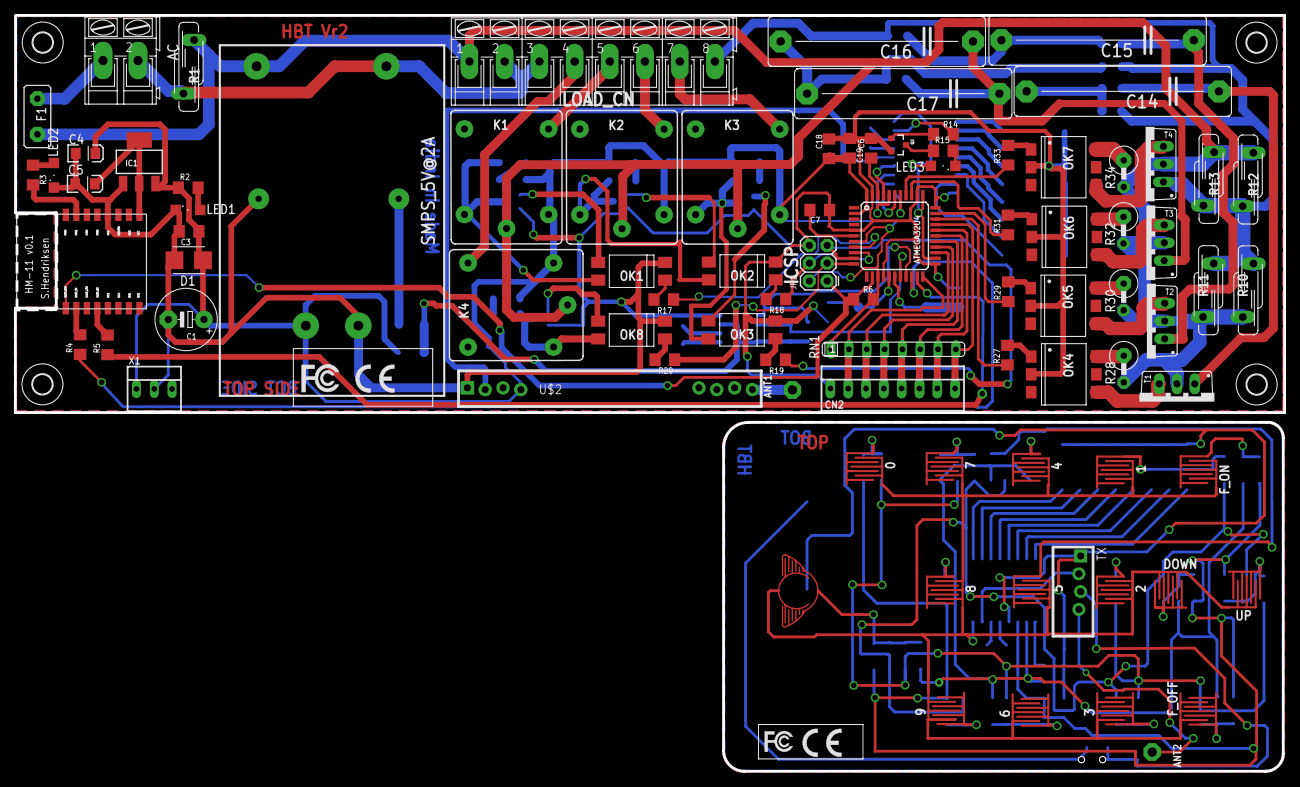
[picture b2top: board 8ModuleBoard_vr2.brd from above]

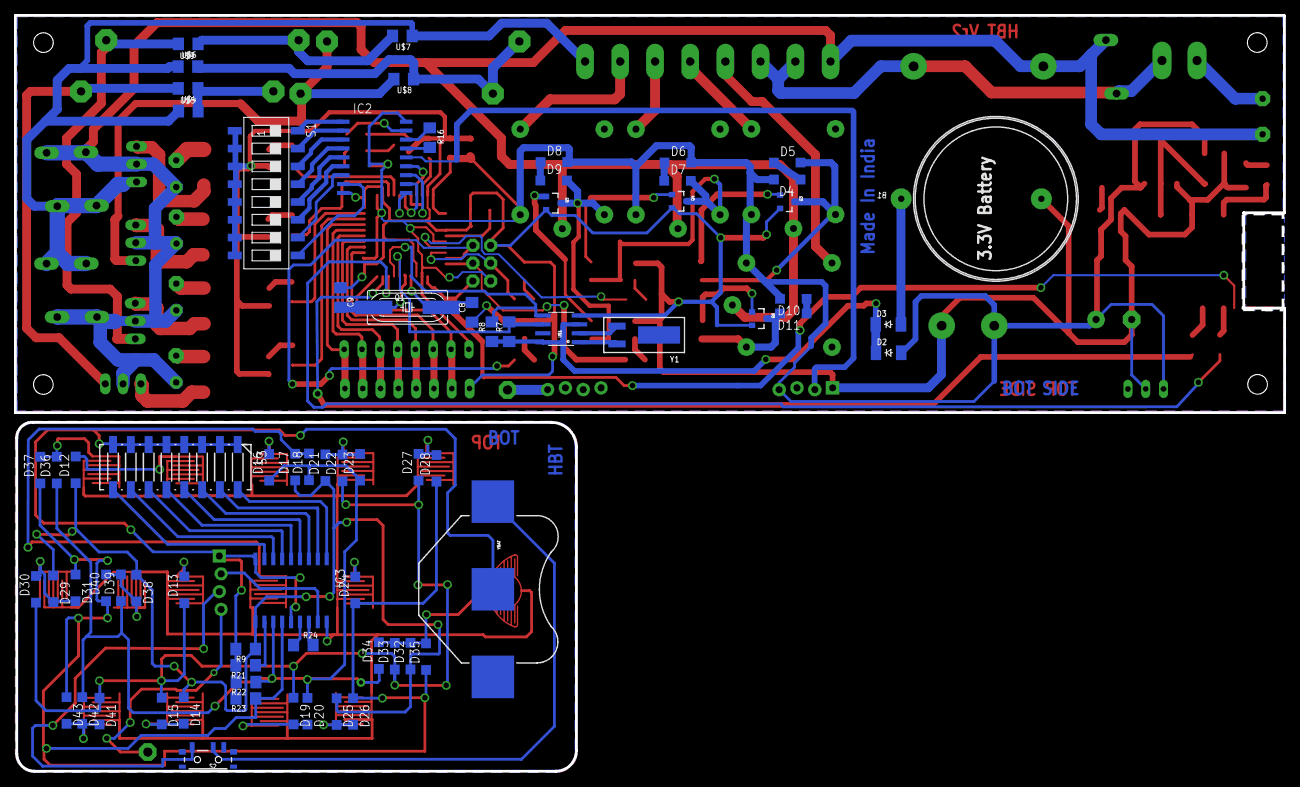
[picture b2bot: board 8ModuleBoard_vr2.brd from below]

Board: 2 copper layers, 181.0 x 107.8 mm, 167 parts (71 on the bottom side), 134 nets.

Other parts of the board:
U$10, U$13: CE-4MM
U$11: FCC_6.1X15MM
U$12: FCC_20X8.35MM

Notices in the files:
parts and their libraries:
PatternAgents-Cypress: License : http://creativecommons.org/licenses/by-sa/3.0
(Creative Commons 3.0)
SparkFun-Capacitors: Licensing: Creative Commons ShareAlike 4.0 International - https://creativecommons.org/licenses/by-sa/4.0
